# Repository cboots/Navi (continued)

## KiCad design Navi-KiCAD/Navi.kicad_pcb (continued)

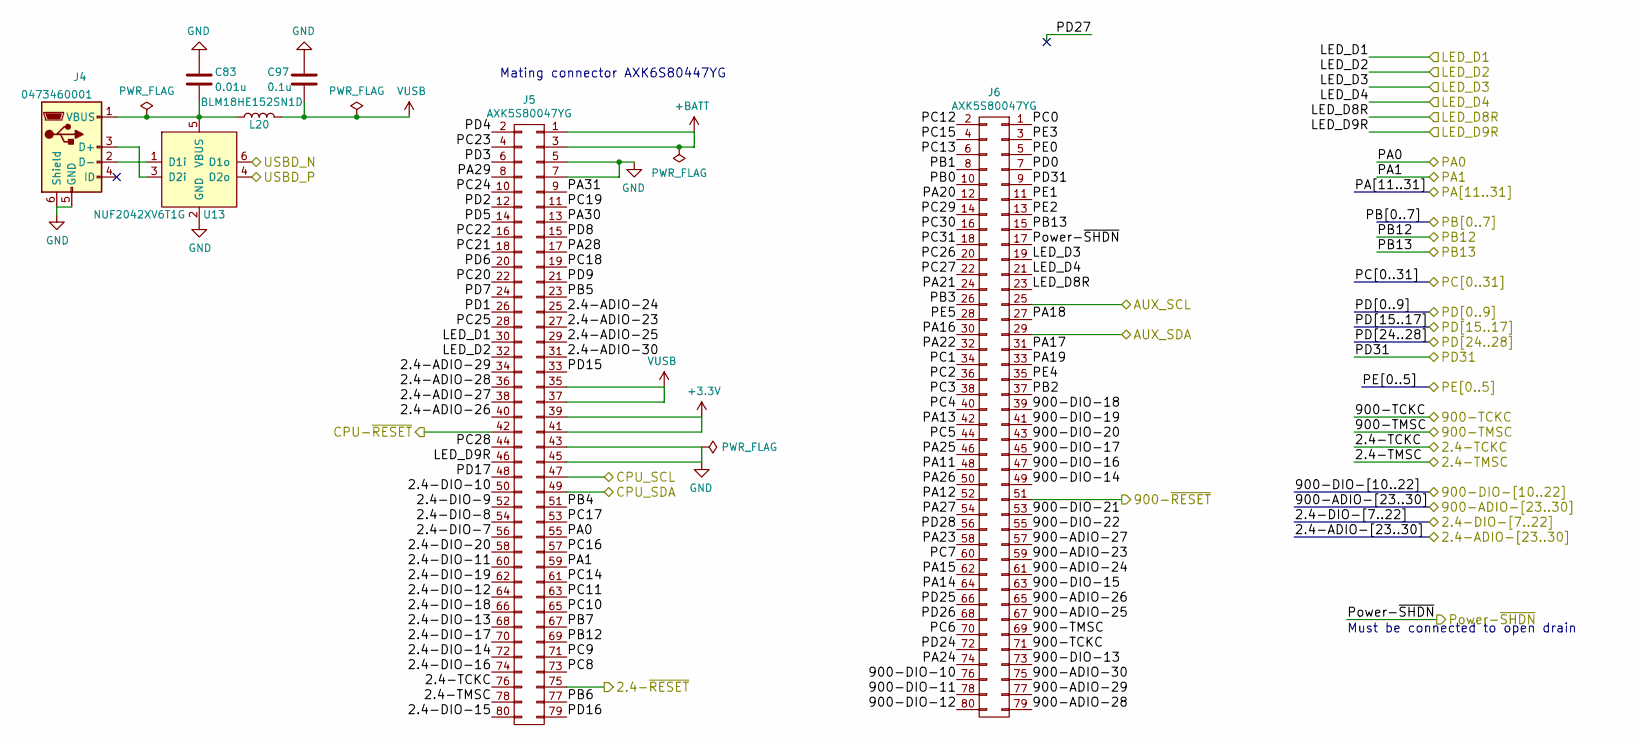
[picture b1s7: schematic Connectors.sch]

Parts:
C83: 0.01u; C_0402; Voltage 50V; Tolerance 20%
C97: 0.1u; C_0402; Voltage 50V; Tolerance 20%
J4: 0473460001; USB_Micro-B_0473460001
J5, J6: AXK5S80047YG
L20: BLM18HE152SN1D; L_0603
U13: NUF2042XV6T1G; SOT-563

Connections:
+3V3: J5.39, J5.41; also elsewhere on the board
+BATT: J5.1, J5.3; also elsewhere on the board
/2.4-TCKC: J5.76; also elsewhere on the board
/2.4-TMSC: J5.78; also elsewhere on the board
/2.4_RESET_EXT: J5.75; also elsewhere on the board
/900-TCKC: J6.71; also elsewhere on the board
/900-TMSC: J6.69; also elsewhere on the board
/900_RESET_EXT: J6.51; also elsewhere on the board
/CPU-SCK: J5.47; also elsewhere on the board
/CPU-SDA: J5.49; also elsewhere on the board
/CPU_RESET_EXT: J5.42; also elsewhere on the board
/Connectors/2.4-ADIO-23: J5.27; also elsewhere on the board
/Connectors/2.4-ADIO-24: J5.25; also elsewhere on the board
/Connectors/2.4-ADIO-25: J5.29; also elsewhere on the board
/Connectors/2.4-ADIO-26: J5.40; also elsewhere on the board
/Connectors/2.4-ADIO-27: J5.38; also elsewhere on the board
/Connectors/2.4-ADIO-28: J5.36; also elsewhere on the board
/Connectors/2.4-ADIO-29: J5.34; also elsewhere on the board
/Connectors/2.4-ADIO-30: J5.31; also elsewhere on the board
/Connectors/2.4-DIO-7: J5.56; also elsewhere on the board
/Connectors/2.4-DIO-8: J5.54; also elsewhere on the board
/Connectors/2.4-DIO-9: J5.52; also elsewhere on the board
/Connectors/2.4-DIO-10: J5.50; also elsewhere on the board
/Connectors/2.4-DIO-11: J5.60; also elsewhere on the board
/Connectors/2.4-DIO-12: J5.64; also elsewhere on the board
/Connectors/2.4-DIO-13: J5.68; also elsewhere on the board
/Connectors/2.4-DIO-14: J5.72; also elsewhere on the board
/Connectors/2.4-DIO-15: J5.80; also elsewhere on the board
/Connectors/2.4-DIO-16: J5.74; also elsewhere on the board
/Connectors/2.4-DIO-17: J5.70; also elsewhere on the board
/Connectors/2.4-DIO-18: J5.66; also elsewhere on the board
/Connectors/2.4-DIO-19: J5.62; also elsewhere on the board
/Connectors/2.4-DIO-20: J5.58; also elsewhere on the board
/Connectors/900-ADIO-23: J6.59; also elsewhere on the board
/Connectors/900-ADIO-24: J6.61; also elsewhere on the board
/Connectors/900-ADIO-25: J6.67; also elsewhere on the board
/Connectors/900-ADIO-26: J6.65; also elsewhere on the board
/Connectors/900-ADIO-27: J6.57; also elsewhere on the board
/Connectors/900-ADIO-28: J6.79; also elsewhere on the board
/Connectors/900-ADIO-29: J6.77; also elsewhere on the board
/Connectors/900-ADIO-30: J6.75; also elsewhere on the board
/Connectors/900-DIO-10: J6.76; also elsewhere on the board
/Connectors/900-DIO-11: J6.78; also elsewhere on the board
/Connectors/900-DIO-12: J6.80; also elsewhere on the board
/Connectors/900-DIO-13: J6.73; also elsewhere on the board
/Connectors/900-DIO-14: J6.49; also elsewhere on the board
/Connectors/900-DIO-15: J6.63; also elsewhere on the board
/Connectors/900-DIO-16: J6.47; also elsewhere on the board
/Connectors/900-DIO-17: J6.45; also elsewhere on the board
/Connectors/900-DIO-18: J6.39; also elsewhere on the board
/Connectors/900-DIO-19: J6.41; also elsewhere on the board
/Connectors/900-DIO-20: J6.43; also elsewhere on the board
/Connectors/900-DIO-21: J6.53; also elsewhere on the board
/Connectors/900-DIO-22: J6.55; also elsewhere on the board
/Connectors/AUX_SCL: J6.25; also elsewhere on the board
/Connectors/AUX_SDA: J6.29; also elsewhere on the board
/Connectors/PA0: J5.55; also elsewhere on the board
/Connectors/PA1: J5.59; also elsewhere on the board
/Connectors/PA11: J6.48; also elsewhere on the board
/Connectors/PA12: J6.52; also elsewhere on the board
/Connectors/PA13: J6.42; also elsewhere on the board
/Connectors/PA14: J6.64; also elsewhere on the board
/Connectors/PA15: J6.62; also elsewhere on the board
/Connectors/PA16: J6.30; also elsewhere on the board
/Connectors/PA17: J6.31; also elsewhere on the board
/Connectors/PA18: J6.27; also elsewhere on the board
/Connectors/PA19: J6.33; also elsewhere on the board
/Connectors/PA20: J6.12; also elsewhere on the board
/Connectors/PA21: J6.24; also elsewhere on the board
/Connectors/PA22: J6.32; also elsewhere on the board
/Connectors/PA23: J6.58; also elsewhere on the board
/Connectors/PA24: J6.74; also elsewhere on the board
/Connectors/PA25: J6.46; also elsewhere on the board
/Connectors/PA26: J6.50; also elsewhere on the board
/Connectors/PA27: J6.54; also elsewhere on the board
/Connectors/PA28: J5.17; also elsewhere on the board
/Connectors/PA29: J5.8; also elsewhere on the board
/Connectors/PA30: J5.13; also elsewhere on the board
/Connectors/PA31: J5.9; also elsewhere on the board
/Connectors/PB0: J6.10; also elsewhere on the board
/Connectors/PB1: J6.8; also elsewhere on the board
/Connectors/PB2: J6.37; also elsewhere on the board
/Connectors/PB3: J6.26; also elsewhere on the board
/Connectors/PB4: J5.51; also elsewhere on the board
/Connectors/PB5: J5.23; also elsewhere on the board
/Connectors/PB6: J5.77; also elsewhere on the board
/Connectors/PB7: J5.67; also elsewhere on the board
/Connectors/PB12: J5.69; also elsewhere on the board
/Connectors/PB13: J6.15; also elsewhere on the board
/Connectors/PC0: J6.1; also elsewhere on the board
/Connectors/PC1: J6.34; also elsewhere on the board
/Connectors/PC2: J6.36; also elsewhere on the board
/Connectors/PC3: J6.38; also elsewhere on the board
/Connectors/PC4: J6.40; also elsewhere on the board
/Connectors/PC5: J6.44; also elsewhere on the board
/Connectors/PC6: J6.70; also elsewhere on the board
/Connectors/PC7: J6.60; also elsewhere on the board
/Connectors/PC8: J5.73; also elsewhere on the board
/Connectors/PC9: J5.71; also elsewhere on the board
/Connectors/PC10: J5.65; also elsewhere on the board
/Connectors/PC11: J5.63; also elsewhere on the board
/Connectors/PC12: J6.2; also elsewhere on the board
/Connectors/PC13: J6.6; also elsewhere on the board
/Connectors/PC14: J5.61; also elsewhere on the board
/Connectors/PC15: J6.4; also elsewhere on the board
/Connectors/PC16: J5.57; also elsewhere on the board
/Connectors/PC17: J5.53; also elsewhere on the board
/Connectors/PC18: J5.19; also elsewhere on the board
/Connectors/PC19: J5.11; also elsewhere on the board
/Connectors/PC20: J5.22; also elsewhere on the board
/Connectors/PC21: J5.18; also elsewhere on the board
/Connectors/PC22: J5.16; also elsewhere on the board
/Connectors/PC23: J5.4; also elsewhere on the board
/Connectors/PC24: J5.10; also elsewhere on the board
/Connectors/PC25: J5.28; also elsewhere on the board
/Connectors/PC26: J6.20; also elsewhere on the board
/Connectors/PC27: J6.22; also elsewhere on the board
/Connectors/PC28: J5.44; also elsewhere on the board
/Connectors/PC29: J6.14; also elsewhere on the board
/Connectors/PC30: J6.16; also elsewhere on the board
/Connectors/PC31: J6.18; also elsewhere on the board
/Connectors/PD0: J6.7; also elsewhere on the board
/Connectors/PD1: J5.26; also elsewhere on the board
/Connectors/PD2: J5.12; also elsewhere on the board
/Connectors/PD3: J5.6; also elsewhere on the board
/Connectors/PD4: J5.2; also elsewhere on the board
/Connectors/PD5: J5.14; also elsewhere on the board
/Connectors/PD6: J5.20; also elsewhere on the board
/Connectors/PD7: J5.24; also elsewhere on the board
/Connectors/PD8: J5.15; also elsewhere on the board
/Connectors/PD9: J5.21; also elsewhere on the board
/Connectors/PD15: J5.33; also elsewhere on the board
/Connectors/PD16: J5.79; also elsewhere on the board
/Connectors/PD17: J5.48; also elsewhere on the board
/Connectors/PD24: J6.72; also elsewhere on the board
/Connectors/PD25: J6.66; also elsewhere on the board
/Connectors/PD26: J6.68; also elsewhere on the board
/Connectors/PD28: J6.56; also elsewhere on the board
/Connectors/PD31: J6.9; also elsewhere on the board
/Connectors/PE0: J6.5; also elsewhere on the board
/Connectors/PE1: J6.11; also elsewhere on the board
/Connectors/PE2: J6.13; also elsewhere on the board
/Connectors/PE3: J6.3; also elsewhere on the board
/Connectors/PE4: J6.35; also elsewhere on the board
/Connectors/PE5: J6.28; also elsewhere on the board
/Connectors/USBD_N: U13.6 (D1o); also elsewhere on the board
/Connectors/USBD_P: U13.4 (D2o); also elsewhere on the board
/LED_D1: J5.30; also elsewhere on the board
/LED_D2: J5.32; also elsewhere on the board
/LED_D3: J6.19; also elsewhere on the board
/LED_D4: J6.21; also elsewhere on the board
/LED_D8R: J6.23; also elsewhere on the board
/LED_D9R: J5.46; also elsewhere on the board
/Power-~SHDN~: J6.17; also elsewhere on the board
GND: C83.1, C97.1, J4.5 (GND), J4.6 (Shield), J5.5, J5.7, J5.43, J5.45, U13.2 (GND); also elsewhere on the board
unnamed: C83.2, J4.1 (VBUS), L20.1, U13.5 (VBUS)
unnamed: J4.2 (D-), U13.1 (D1i)
unnamed: J4.3 (D+), U13.3 (D2i)
VUSB: C97.2, J5.35, J5.37, L20.2; also elsewhere on the board

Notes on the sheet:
Mating connector AXK6S80447YG
Must be connected to open drain

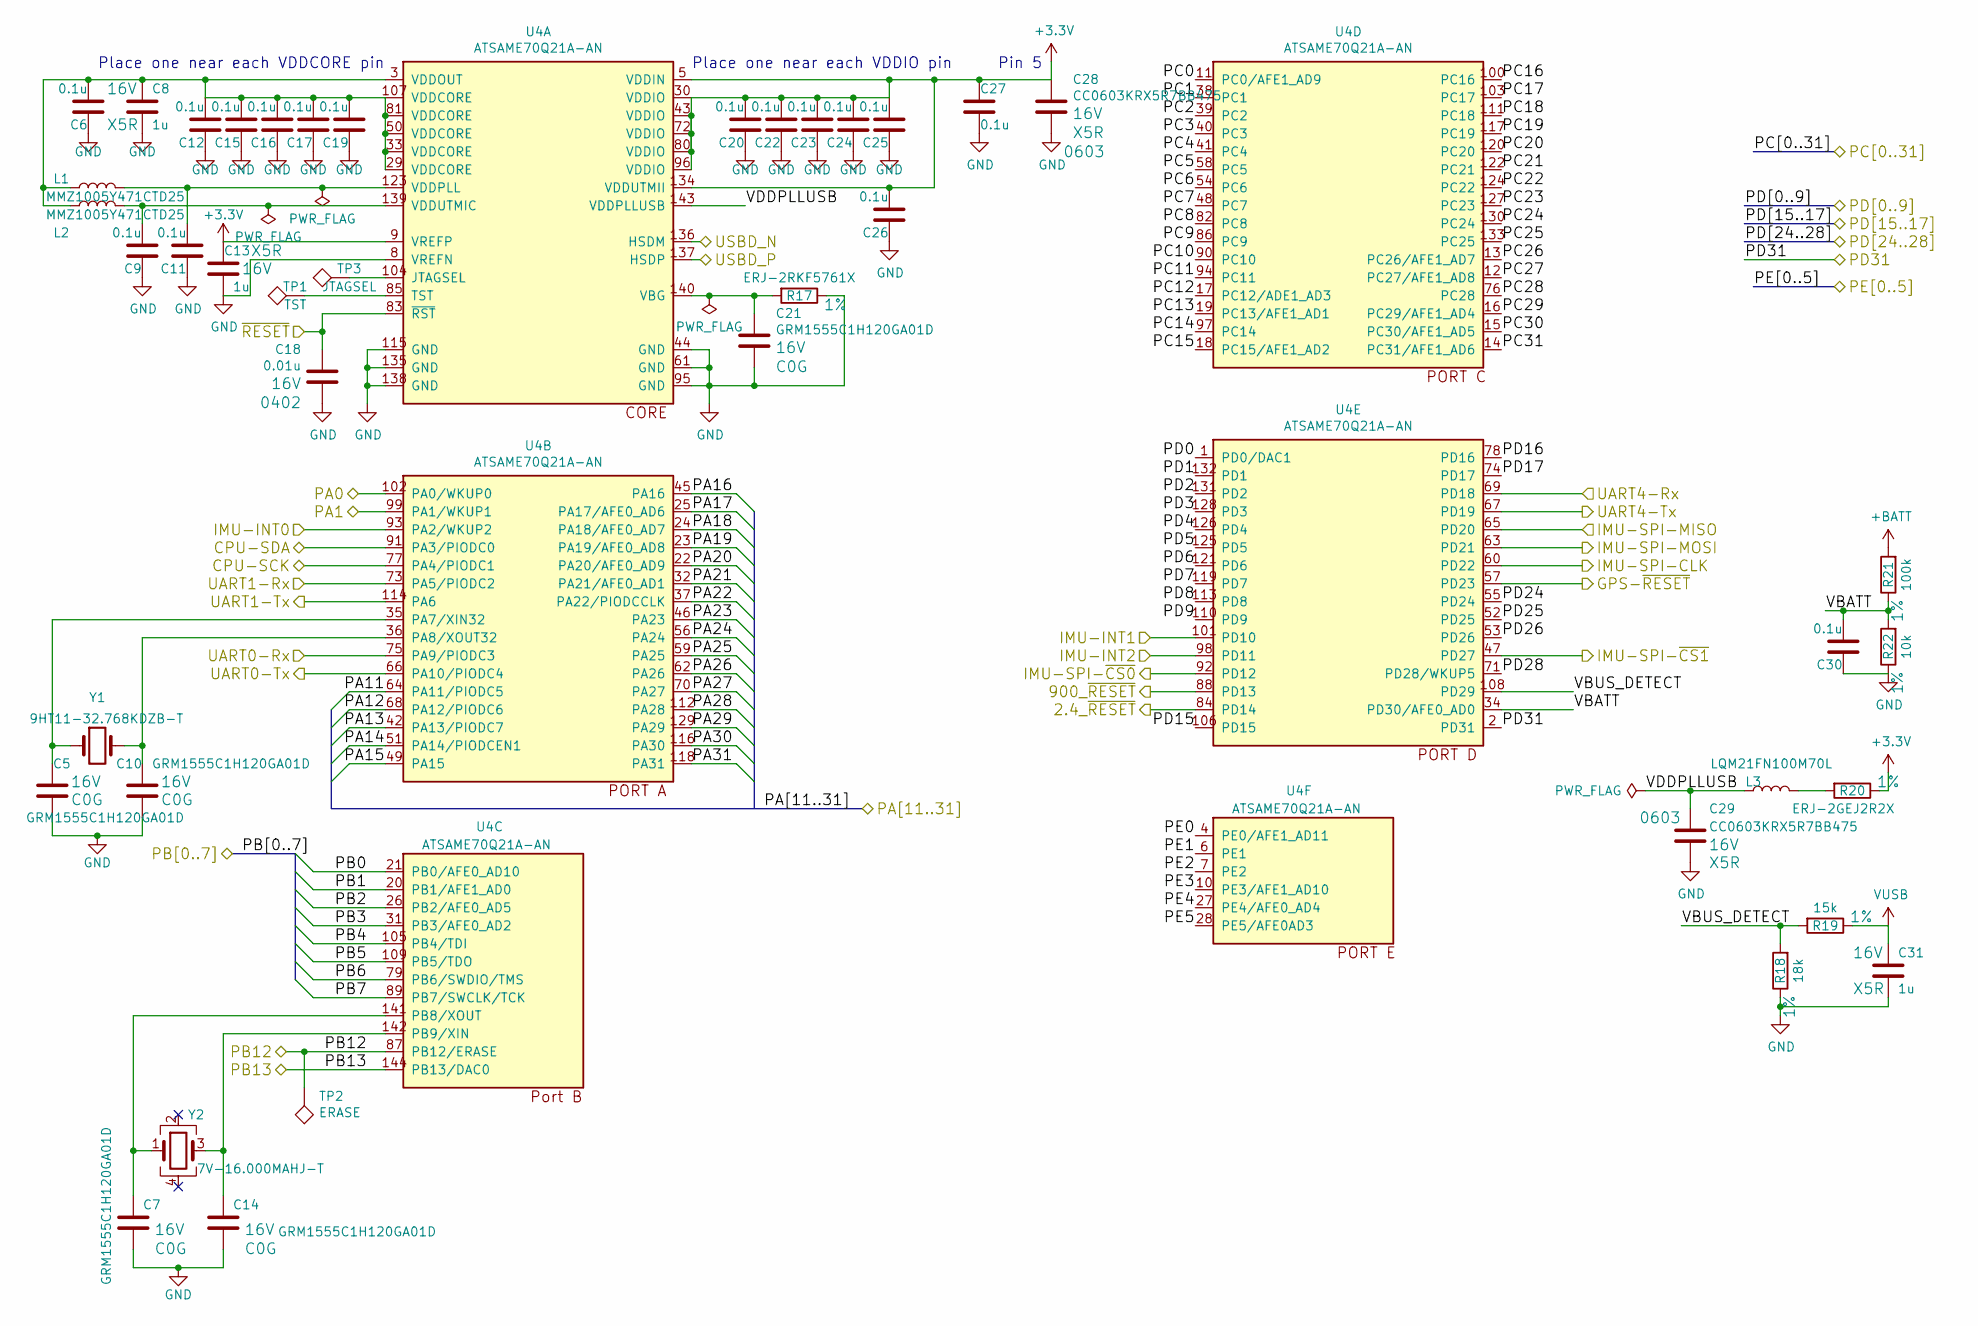
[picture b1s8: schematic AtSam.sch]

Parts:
C5, C7, C10, C14, C21: GRM1555C1H120GA01D; C_0402; Voltage 16V; Tolerance 20%
C6, C9, C11, C12, C15, C16, C17, C19, C20, C22, C23, C24, C25, C26, C27, C30: 0.1u; C_0402; Voltage 16V; Tolerance 20%
C8, C13, C31: 1u; C_0402; Voltage 16V; Tolerance 20%
C18: 0.01u; C_0402; Voltage 16V; Tolerance 20%
C28, C29: CC0603KRX5R7BB475; C_0603; Voltage 16V; Tolerance 20%
L1, L2: MMZ1005Y471CTD25; L_0402
L3: LQM21FN100M70L; L_0805
R17: ERJ-2RKF5761X; R_0402; Tolerance 1%; Voltage 16V
R18: 18k; R_0402; Tolerance 1%; Voltage 16V
R19: 15k; R_0402; Tolerance 1%; Voltage 16V
R20: ERJ-2GEJ2R2X; R_0402; Tolerance 1%; Voltage 16V
R21: 100k; R_0402; Tolerance 1%; Voltage 50V
R22: 10k; R_0402; Tolerance 1%; Voltage 50V
TP1: TST; Measurement_Point_Round-SMD-Pad_Very_Small
TP2: ERASE; Measurement_Point_Round-SMD-Pad_Very_Small
TP3: JTAGSEL; Measurement_Point_Round-SMD-Pad_Very_Small
U4: ATSAME70Q21A-AN; LQFP-144_20x20mm_Pitch0.5mm
Y1: 9HT11-32.768KDZB-T; Crystal_SMD_2012-2pin_2.0x1.2mm
Y2: 7V-16.000MAHJ-T; Crystal_SMD_3225-4pin_3.2x2.5mm

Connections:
+3V3: C13.1, C20.1, C22.1, C23.1, C24.1, C25.1, C26.1, C27.2, C28.2, R20.1, U4.5 (VDDIN), U4.9 (VREFP), U4.30 (VDDIO), U4.43 (VDDIO), U4.72 (VDDIO), U4.80 (VDDIO), U4.96 (VDDIO), U4.134 (VDDUTMII); also elsewhere on the board
+BATT: R21.2; also elsewhere on the board
/2.4G-Rx: U4.66 (PA10/PIODC4); also elsewhere on the board
/2.4G-Tx: U4.75 (PA9/PIODC3); also elsewhere on the board
/2.4_RESET_CPU: U4.84 (PD14); also elsewhere on the board
/900M-Rx: U4.67 (PD19); also elsewhere on the board
/900M-Tx: U4.69 (PD18); also elsewhere on the board
/900_RESET_CPU: U4.88 (PD13); also elsewhere on the board
/CPU-SCK: U4.77 (PA4/PIODC1); also elsewhere on the board
/CPU-SDA: U4.91 (PA3/PIODC0); also elsewhere on the board
/Connectors/PA0: U4.102 (PA0/WKUP0); also elsewhere on the board
/Connectors/PA1: U4.99 (PA1/WKUP1); also elsewhere on the board
/Connectors/PA11: U4.64 (PA11/PIODC5); also elsewhere on the board
/Connectors/PA12: U4.68 (PA12/PIODC6); also elsewhere on the board
/Connectors/PA13: U4.42 (PA13/PIODC7); also elsewhere on the board
/Connectors/PA14: U4.51 (PA14/PIODCEN1); also elsewhere on the board
/Connectors/PA15: U4.49 (PA15); also elsewhere on the board
/Connectors/PA16: U4.45 (PA16); also elsewhere on the board
/Connectors/PA17: U4.25 (PA17/AFE0_AD6); also elsewhere on the board
/Connectors/PA18: U4.24 (PA18/AFE0_AD7); also elsewhere on the board
/Connectors/PA19: U4.23 (PA19/AFE0_AD8); also elsewhere on the board
/Connectors/PA20: U4.22 (PA20/AFE0_AD9); also elsewhere on the board
/Connectors/PA21: U4.32 (PA21/AFE0_AD1); also elsewhere on the board
/Connectors/PA22: U4.37 (PA22/PIODCCLK); also elsewhere on the board
/Connectors/PA23: U4.46 (PA23); also elsewhere on the board
/Connectors/PA24: U4.56 (PA24); also elsewhere on the board
/Connectors/PA25: U4.59 (PA25); also elsewhere on the board
/Connectors/PA26: U4.62 (PA26); also elsewhere on the board
/Connectors/PA27: U4.70 (PA27); also elsewhere on the board
/Connectors/PA28: U4.112 (PA28); also elsewhere on the board
/Connectors/PA29: U4.129 (PA29); also elsewhere on the board
/Connectors/PA30: U4.116 (PA30); also elsewhere on the board
/Connectors/PA31: U4.118 (PA31); also elsewhere on the board
/Connectors/PB0: U4.21 (PB0/AFE0_AD10); also elsewhere on the board
/Connectors/PB1: U4.20 (PB1/AFE1_AD0); also elsewhere on the board
/Connectors/PB2: U4.26 (PB2/AFE0_AD5); also elsewhere on the board
/Connectors/PB3: U4.31 (PB3/AFE0_AD2); also elsewhere on the board
/Connectors/PB4: U4.105 (PB4/TDI); also elsewhere on the board
/Connectors/PB5: U4.109 (PB5/TDO); also elsewhere on the board
/Connectors/PB6: U4.79 (PB6/SWDIO/TMS); also elsewhere on the board
/Connectors/PB7: U4.89 (PB7/SWCLK/TCK); also elsewhere on the board
/Connectors/PB12: TP2.1, U4.87 (PB12/ERASE); also elsewhere on the board
/Connectors/PB13: U4.144 (PB13/DAC0); also elsewhere on the board
/Connectors/PC0: U4.11 (PC0/AFE1_AD9); also elsewhere on the board
/Connectors/PC1: U4.38 (PC1); also elsewhere on the board
/Connectors/PC2: U4.39 (PC2); also elsewhere on the board
/Connectors/PC3: U4.40 (PC3); also elsewhere on the board
/Connectors/PC4: U4.41 (PC4); also elsewhere on the board
/Connectors/PC5: U4.58 (PC5); also elsewhere on the board
/Connectors/PC6: U4.54 (PC6); also elsewhere on the board
/Connectors/PC7: U4.48 (PC7); also elsewhere on the board
/Connectors/PC8: U4.82 (PC8); also elsewhere on the board
/Connectors/PC9: U4.86 (PC9); also elsewhere on the board
/Connectors/PC10: U4.90 (PC10); also elsewhere on the board
/Connectors/PC11: U4.94 (PC11); also elsewhere on the board
/Connectors/PC12: U4.17 (PC12/ADE1_AD3); also elsewhere on the board
/Connectors/PC13: U4.19 (PC13/AFE1_AD1); also elsewhere on the board
/Connectors/PC14: U4.97 (PC14); also elsewhere on the board
/Connectors/PC15: U4.18 (PC15/AFE1_AD2); also elsewhere on the board
/Connectors/PC16: U4.100 (PC16); also elsewhere on the board
/Connectors/PC17: U4.103 (PC17); also elsewhere on the board
/Connectors/PC18: U4.111 (PC18); also elsewhere on the board
/Connectors/PC19: U4.117 (PC19); also elsewhere on the board
/Connectors/PC20: U4.120 (PC20); also elsewhere on the board
/Connectors/PC21: U4.122 (PC21); also elsewhere on the board
/Connectors/PC22: U4.124 (PC22); also elsewhere on the board
/Connectors/PC23: U4.127 (PC23); also elsewhere on the board
/Connectors/PC24: U4.130 (PC24); also elsewhere on the board
/Connectors/PC25: U4.133 (PC25); also elsewhere on the board
/Connectors/PC26: U4.13 (PC26/AFE1_AD7); also elsewhere on the board
/Connectors/PC27: U4.12 (PC27/AFE1_AD8); also elsewhere on the board
/Connectors/PC28: U4.76 (PC28); also elsewhere on the board
/Connectors/PC29: U4.16 (PC29/AFE1_AD4); also elsewhere on the board
/Connectors/PC30: U4.15 (PC30/AFE1_AD5); also elsewhere on the board
/Connectors/PC31: U4.14 (PC31/AFE1_AD6); also elsewhere on the board
/Connectors/PD0: U4.1 (PD0/DAC1); also elsewhere on the board
/Connectors/PD1: U4.132 (PD1); also elsewhere on the board
/Connectors/PD2: U4.131 (PD2); also elsewhere on the board
/Connectors/PD3: U4.128 (PD3); also elsewhere on the board
/Connectors/PD4: U4.126 (PD4); also elsewhere on the board
/Connectors/PD5: U4.125 (PD5); also elsewhere on the board
/Connectors/PD6: U4.121 (PD6); also elsewhere on the board
/Connectors/PD7: U4.119 (PD7); also elsewhere on the board
/Connectors/PD8: U4.113 (PD8); also elsewhere on the board
/Connectors/PD9: U4.110 (PD9); also elsewhere on the board
/Connectors/PD15: U4.106 (PD15); also elsewhere on the board
/Connectors/PD16: U4.78 (PD16); also elsewhere on the board
/Connectors/PD17: U4.74 (PD17); also elsewhere on the board
/Connectors/PD24: U4.55 (PD24); also elsewhere on the board
/Connectors/PD25: U4.52 (PD25); also elsewhere on the board
/Connectors/PD26: U4.53 (PD26); also elsewhere on the board
/Connectors/PD28: U4.71 (PD28/WKUP5); also elsewhere on the board
/Connectors/PD31: U4.2 (PD31); also elsewhere on the board
/Connectors/PE0: U4.4 (PE0/AFE1_AD11); also elsewhere on the board
/Connectors/PE1: U4.6 (PE1); also elsewhere on the board
/Connectors/PE2: U4.7 (PE2); also elsewhere on the board
/Connectors/PE3: U4.10 (PE3/AFE1_AD10); also elsewhere on the board
/Connectors/PE4: U4.27 (PE4/AFE0_AD4); also elsewhere on the board
/Connectors/PE5: U4.28 (PE5/AFE0AD3); also elsewhere on the board
/Connectors/USBD_N: U4.136 (HSDM); also elsewhere on the board
/Connectors/USBD_P: U4.137 (HSDP); also elsewhere on the board
/GNC_Processor/GPS-~RESET: U4.57 (PD23); also elsewhere on the board
/GNC_Processor/IMU-INT0: U4.93 (PA2/WKUP2); also elsewhere on the board
/GNC_Processor/IMU-INT1: U4.101 (PD10); also elsewhere on the board
/GNC_Processor/IMU-INT2: U4.98 (PD11); also elsewhere on the board
/GNC_Processor/IMU-SPI-CLK: U4.60 (PD22); also elsewhere on the board
/GNC_Processor/IMU-SPI-MISO: U4.65 (PD20); also elsewhere on the board
/GNC_Processor/IMU-SPI-MOSI: U4.63 (PD21); also elsewhere on the board
/GNC_Processor/IMU-SPI-~CS0: U4.92 (PD12); also elsewhere on the board
/GNC_Processor/IMU-SPI-~CS1: U4.47 (PD27); also elsewhere on the board
/GNC_Processor/VBATT: C30.1, R21.1, R22.2, U4.34 (PD30/AFE0_AD0)
/GNC_Processor/VBUS_DETECT: R18.2, R19.2, U4.108 (PD29)
/GNC_Processor/VDDPLLUSB: C29.2, L3.1, U4.143 (VDDPLLUSB)
/GNC_Processor/~RESET: C18.1, U4.83 (~RST); also elsewhere on the board
/GPS/GPS-Rx: U4.114 (PA6); also elsewhere on the board
/GPS/GPS-Tx: U4.73 (PA5/PIODC2); also elsewhere on the board
GND: C5.1, C6.2, C7.1, C8.2, C9.2, C10.1, C11.2, C12.2, C13.2, C14.1, C15.2, C16.2, C17.2, C18.2, C19.2, C20.2, C21.1, C22.2, C23.2, C24.2, C25.2, C26.2, C27.1, C28.1, C29.1, C30.2, C31.2, R17.1, R18.1, R22.1, U4.8 (VREFN), U4.44 (GND), U4.61 (GND), U4.95 (GND), U4.115 (GND), U4.135 (GND), U4.138 (GND); also elsewhere on the board
unnamed: C5.2, U4.35 (PA7/XIN32), Y1.1
unnamed: C7.2, U4.141 (PB8/XOUT), Y2.1
unnamed: C9.1, L2.2, U4.139 (VDDUTMIC)
unnamed: C10.2, U4.36 (PA8/XOUT32), Y1.2
unnamed: C11.1, L1.2, U4.123 (VDDPLL)
unnamed: C6.1, C8.1, C12.1, C15.1, C16.1, C17.1, C19.1, L1.1, L2.1, U4.3 (VDDOUT), U4.29 (VDDCORE), U4.33 (VDDCORE), U4.50 (VDDCORE), U4.81 (VDDCORE), U4.107 (VDDCORE)
unnamed: C14.2, U4.142 (PB9/XIN), Y2.3
unnamed: C21.2, R17.2, U4.140 (VBG)
unnamed: L3.2, R20.2
unnamed: TP1.1, U4.85 (TST)
unnamed: TP3.1, U4.104 (JTAGSEL)
VUSB: C31.1, R19.1; also elsewhere on the board

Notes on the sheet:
Pin 5
Place one near each VDDIO pin
Place one near each VDDCORE pin

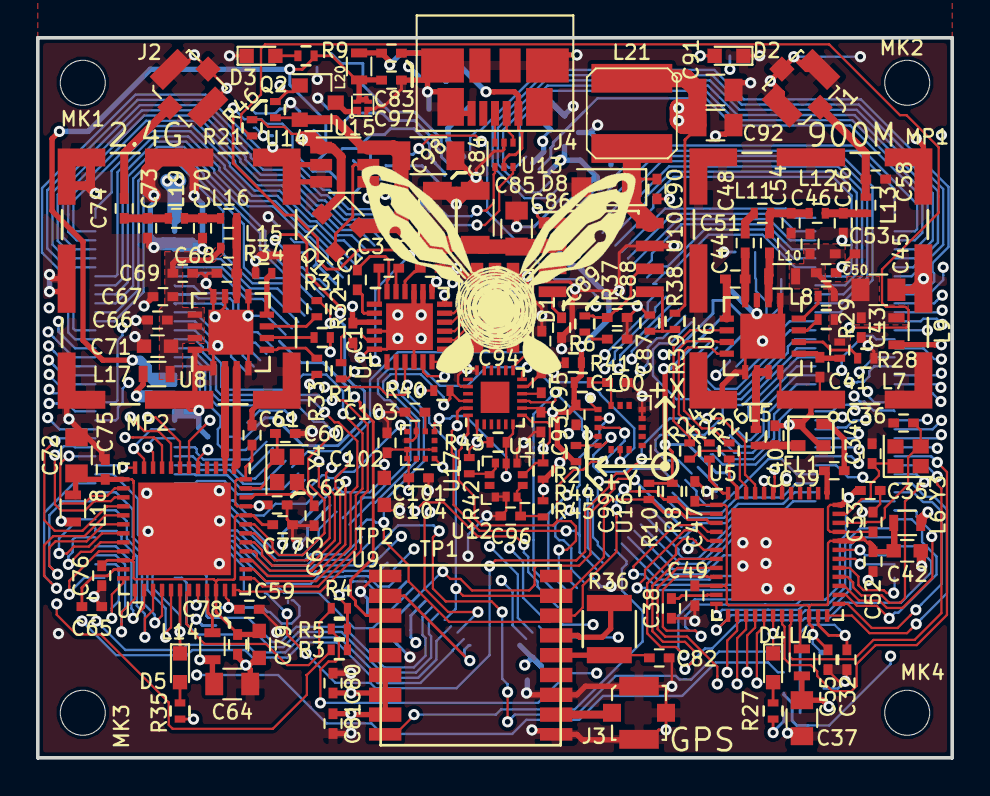
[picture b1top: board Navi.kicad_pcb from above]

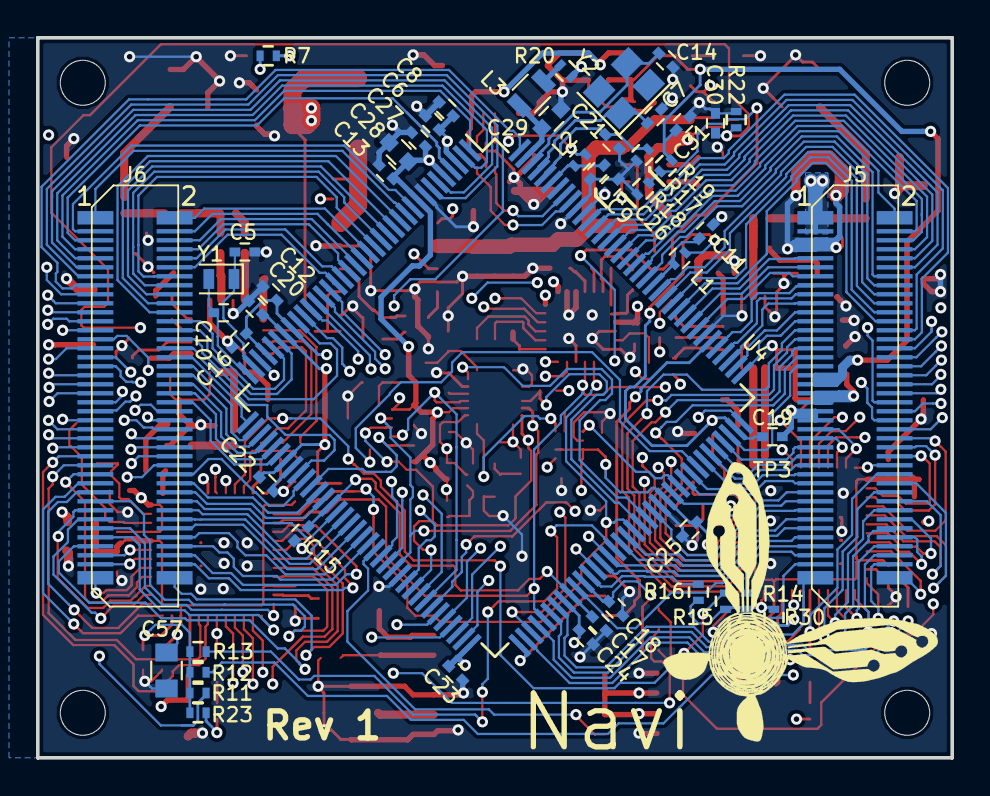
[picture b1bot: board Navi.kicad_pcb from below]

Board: 4 copper layers, 50.8 x 40.0 mm, 216 parts (52 on the bottom side), 277 nets.

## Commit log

2017-03-16 Initial commit in new directory.
2017-03-16 Cleaned up library references.
2017-03-16 Some BOM consolidation.
2017-03-17 Completed key routing.
2017-03-18 Some more GNC processor routing
2017-03-18 Additional routing
2017-03-28 Upgraded to 9 channel RGB driver. Broke out signals for LSM303 and LSM6DS3
2017-04-18 Added additional sensors
2017-04-23 Tweaked pinouts and finished routing known connectors. Now for the remaining IO.
2017-04-26 Finished reroute
2017-04-26 Printed circuitboard.
2017-04-30 Cleaned up silkscreen.
2017-04-30 Rebuilt outputs
2017-04-30 Cleaned up 3D models and rebuilt outputs.
